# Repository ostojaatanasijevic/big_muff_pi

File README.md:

# Big Muff Pi clone

## Schematic

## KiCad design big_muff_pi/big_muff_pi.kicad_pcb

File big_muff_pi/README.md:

# Big Muff Pi clone

## Schematic

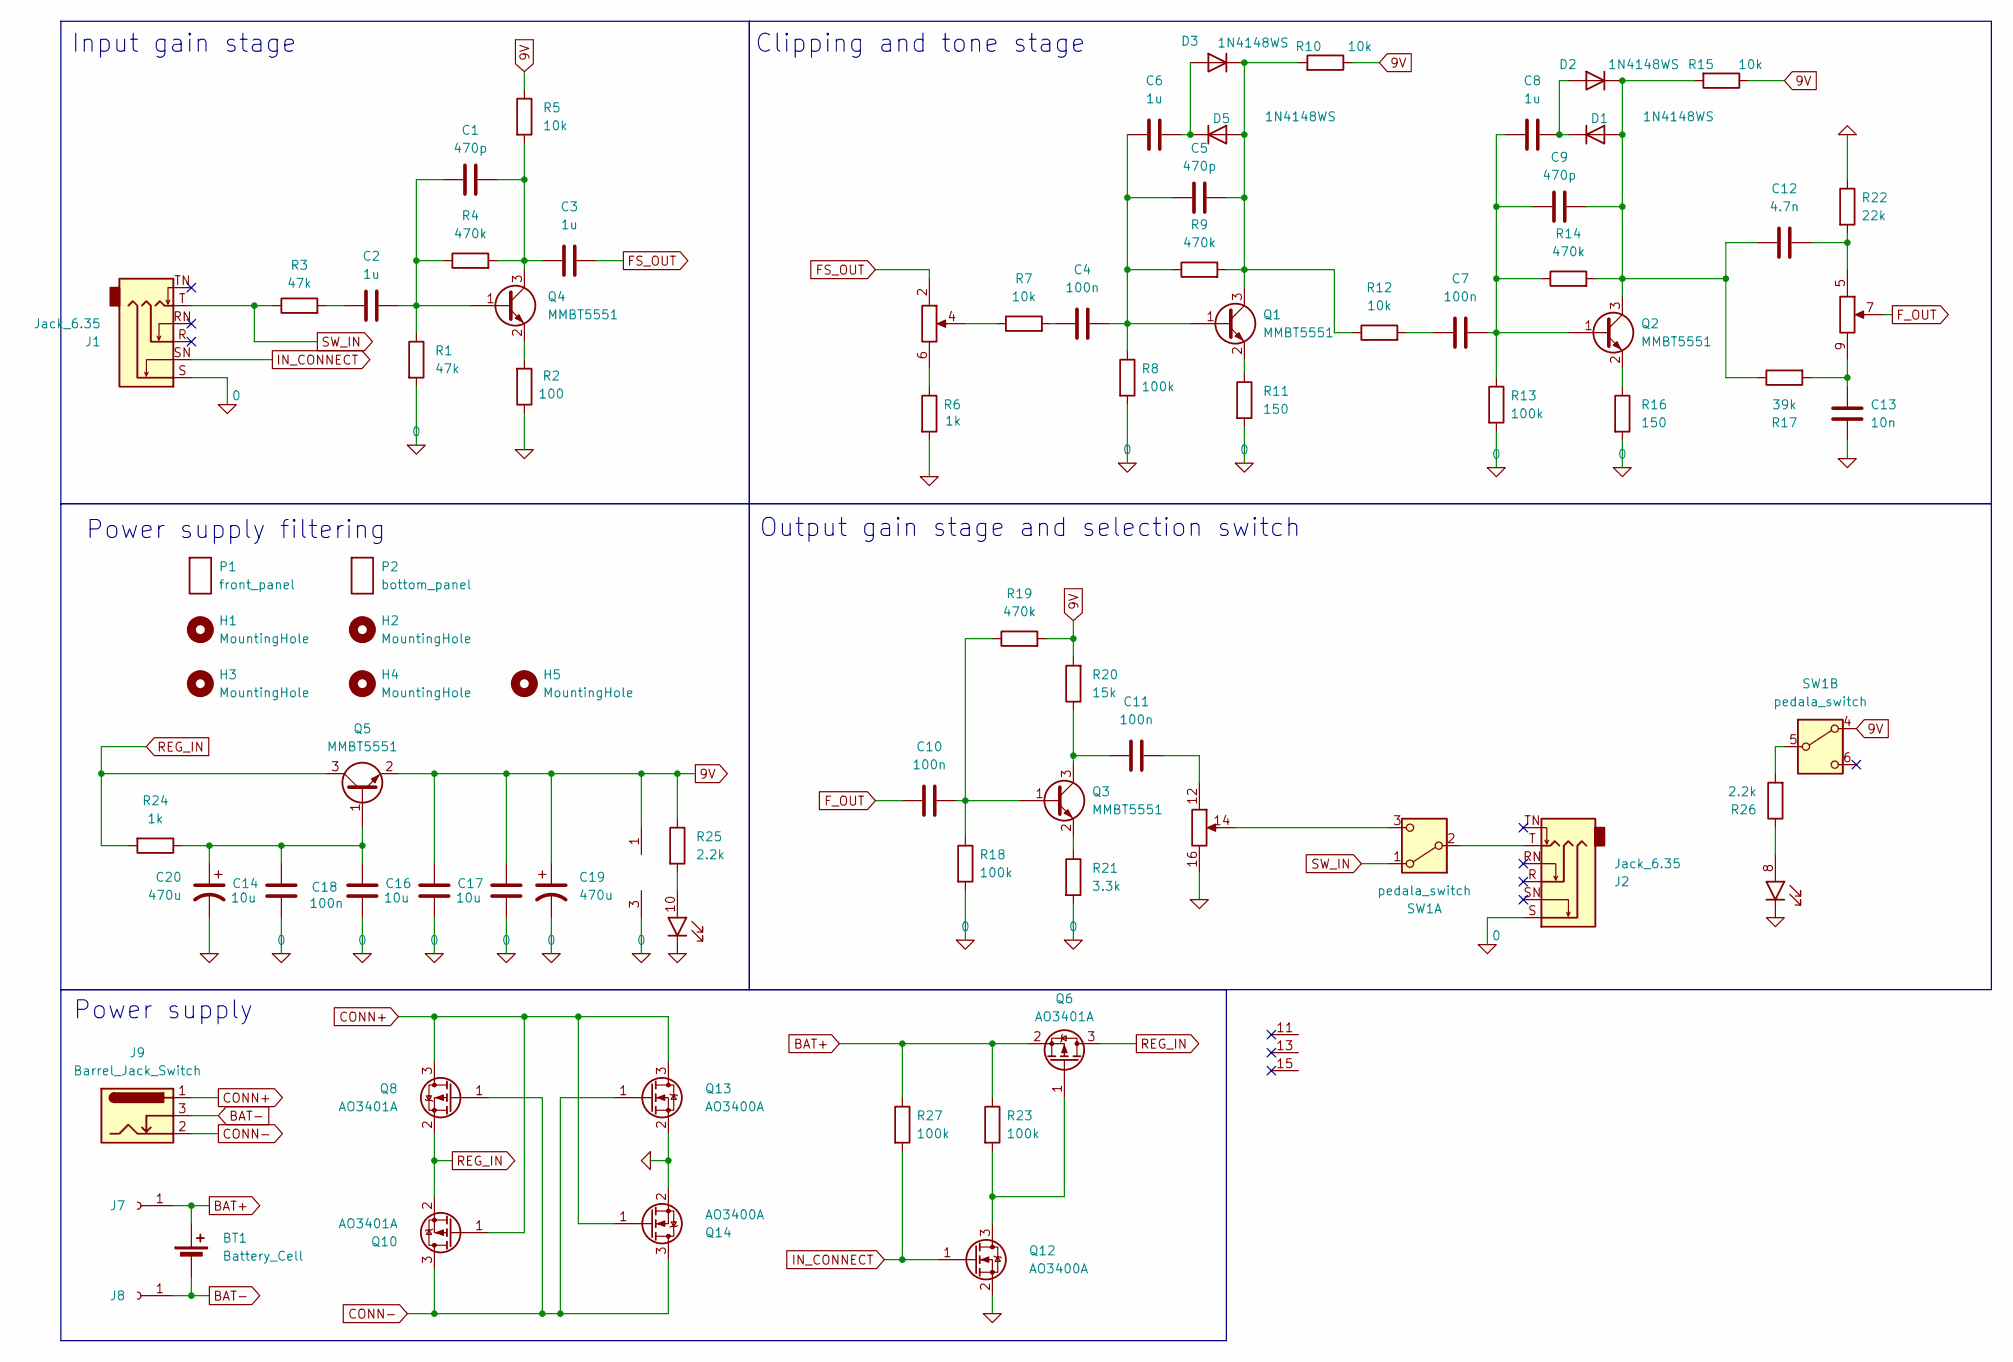
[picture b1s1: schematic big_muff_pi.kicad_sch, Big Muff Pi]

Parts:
BT1: Battery_Cell; BatteryHolder_Eagle_12BH611-GR
C1, C5, C9: 470p; C_0603_1608Metric_Pad1.08x0.95mm_HandSolder; LCSC C1620
C2, C3, C6, C8: 1u; C_0603_1608Metric_Pad1.08x0.95mm_HandSolder; LCSC C15849
C4, C7, C10, C11, C18: 100n; C_0603_1608Metric_Pad1.08x0.95mm_HandSolder; LCSC C14663
C12: 4.7n; C_0603_1608Metric_Pad1.08x0.95mm_HandSolder; LCSC C53987
C13: 10n; C_0603_1608Metric_Pad1.08x0.95mm_HandSolder; LCSC C57112
C14, C16, C17: 10u; C_0603_1608Metric_Pad1.08x0.95mm_HandSolder; LCSC C96446
C19, C20: 470u; CP_Radial_D8.0mm_P3.50mm
D1, D2, D3, D5: 1N4148WS; D_SOD-323; LCSC C2128
H1, H2, H3, H4, H5: MountingHole; M3_hole_with_spacer
J1, J2: Jack_6.35; Jack_6.35mm
J6: top_panel_connector; IDC-Header_2x08_P2.54mm_Vertical
J7, J8: Conn_01x01_Socket; TestPoint_THTPad_D2.5mm_Drill1.2mm
J9: Barrel_Jack_Switch; BarrelJack
P1: front_panel; front_plate
P2: bottom_panel; bottom_plate
Q1, Q2, Q3, Q4, Q5: MMBT5551; SOT-23; LCSC C2145
Q6, Q8, Q10: AO3401A; SOT-23; LCSC C15127
Q12, Q13, Q14: AO3400A; SOT-23; LCSC C20917
R1, R3: 47k; R_0603_1608Metric_Pad0.98x0.95mm_HandSolder; LCSC C25819
R2: 100; R_0603_1608Metric_Pad0.98x0.95mm_HandSolder; LCSC C22775
R4, R9, R14, R19: 470k; R_0603_1608Metric_Pad0.98x0.95mm_HandSolder; LCSC C23178
R5, R7, R10, R12, R15: 10k; R_0603_1608Metric_Pad0.98x0.95mm_HandSolder; LCSC C25804
R6, R24: 1k; R_0603_1608Metric_Pad0.98x0.95mm_HandSolder; LCSC C21190
R8, R13, R18, R23, R27: 100k; R_0603_1608Metric_Pad0.98x0.95mm_HandSolder; LCSC C25803
R11, R16: 150; R_0603_1608Metric_Pad0.98x0.95mm_HandSolder; LCSC C22808
R17: 39k; R_0603_1608Metric_Pad0.98x0.95mm_HandSolder; LCSC C23153
R20: 15k; R_0603_1608Metric_Pad0.98x0.95mm_HandSolder; LCSC C22809
R21: 3.3k; R_0603_1608Metric_Pad0.98x0.95mm_HandSolder; LCSC C22978
R22: 22k; R_0603_1608Metric_Pad0.98x0.95mm_HandSolder; LCSC C31850
R25, R26: 2.2k; R_0603_1608Metric_Pad0.98x0.95mm_HandSolder; LCSC C4190
SW1: pedala_switch; foot_switch_tht_no_pad

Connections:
0: C13.1, C14.2, C16.2, C17.2, C18.1, C19.2, C20.2, J1.S, J2.S, J6.3 (GND), J6.16, Q12.2 (S), Q13.2 (S), Q14.2 (S), R1.2, R2.1, R6.2, R8.2, R11.2, R13.2, R16.2, R18.2, R21.2, R22.1
9V: C16.1, C17.1, C19.1, J6.1 (VCC), Q5.2 (E), R5.1, R10.1, R15.1, R19.2, R20.2, R25.1, SW1.4 (A)
BAT+: BT1.1 (+), J7.1, Q6.2 (S), R23.1, R27.1
BAT-: BT1.2 (-), J8.1, J9.3
CONN+: J9.1, Q8.3 (D), Q10.1 (G), Q13.3 (D), Q14.1 (G)
CONN-: J9.2, Q8.1 (G), Q10.3 (D), Q13.1 (G), Q14.3 (D)
FS_OUT: C3.2, J6.2
F_OUT: C10.1, J6.7
IN_CONNECT: J1.SN, Q12.1 (G), R27.2
unnamed: C2.1, R3.2
unnamed: C4.1, R7.2
unnamed: C7.1, R12.2
unnamed: C9.2, C12.1, D1.2 (A), D2.1 (K), Q2.3 (C), R14.2, R15.2, R17.1
unnamed: C8.2, D1.1 (K), D2.2 (A)
unnamed: C6.2, D3.2 (A), D5.1 (K)
unnamed: C5.2, D3.1 (K), D5.2 (A), Q1.3 (C), R9.2, R10.2, R12.1
unnamed: J6.4, R7.1
unnamed: J6.6, R6.1
unnamed: C12.2, J6.5, R22.2
unnamed: C13.2, J6.9, R17.2
unnamed: C11.2, J6.12
unnamed: J6.14, SW1.3 (C)
unnamed: J6.8, R26.1
unnamed: J6.10, R25.2
unnamed: C4.2, C5.1, C6.1, Q1.1 (B), R8.1, R9.1
unnamed: Q1.2 (E), R11.1
unnamed: C7.2, C8.1, C9.1, Q2.1 (B), R13.1, R14.1
unnamed: Q2.2 (E), R16.1
unnamed: C10.2, Q3.1 (B), R18.1, R19.1
unnamed: C11.1, Q3.3 (C), R20.1
unnamed: Q3.2 (E), R21.1
unnamed: C1.1, C2.2, Q4.1 (B), R1.1, R4.1
unnamed: C1.2, C3.1, Q4.3 (C), R4.2, R5.2
unnamed: Q4.2 (E), R2.2
unnamed: C14.1, C18.2, C20.1, Q5.1 (B), R24.1
unnamed: Q6.1 (G), Q12.3 (D), R23.2
unnamed: J2.T, SW1.2 (B)
unnamed: R26.2, SW1.5 (B)
REG_IN: Q5.3 (C), Q6.3 (D), Q8.2 (S), Q10.2 (S), R24.2
SW_IN: J1.T, R3.1, SW1.1 (A)

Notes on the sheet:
Power supply filtering
Input gain stage
Output gain stage and selection switch
Clipping and tone stage
Power supply

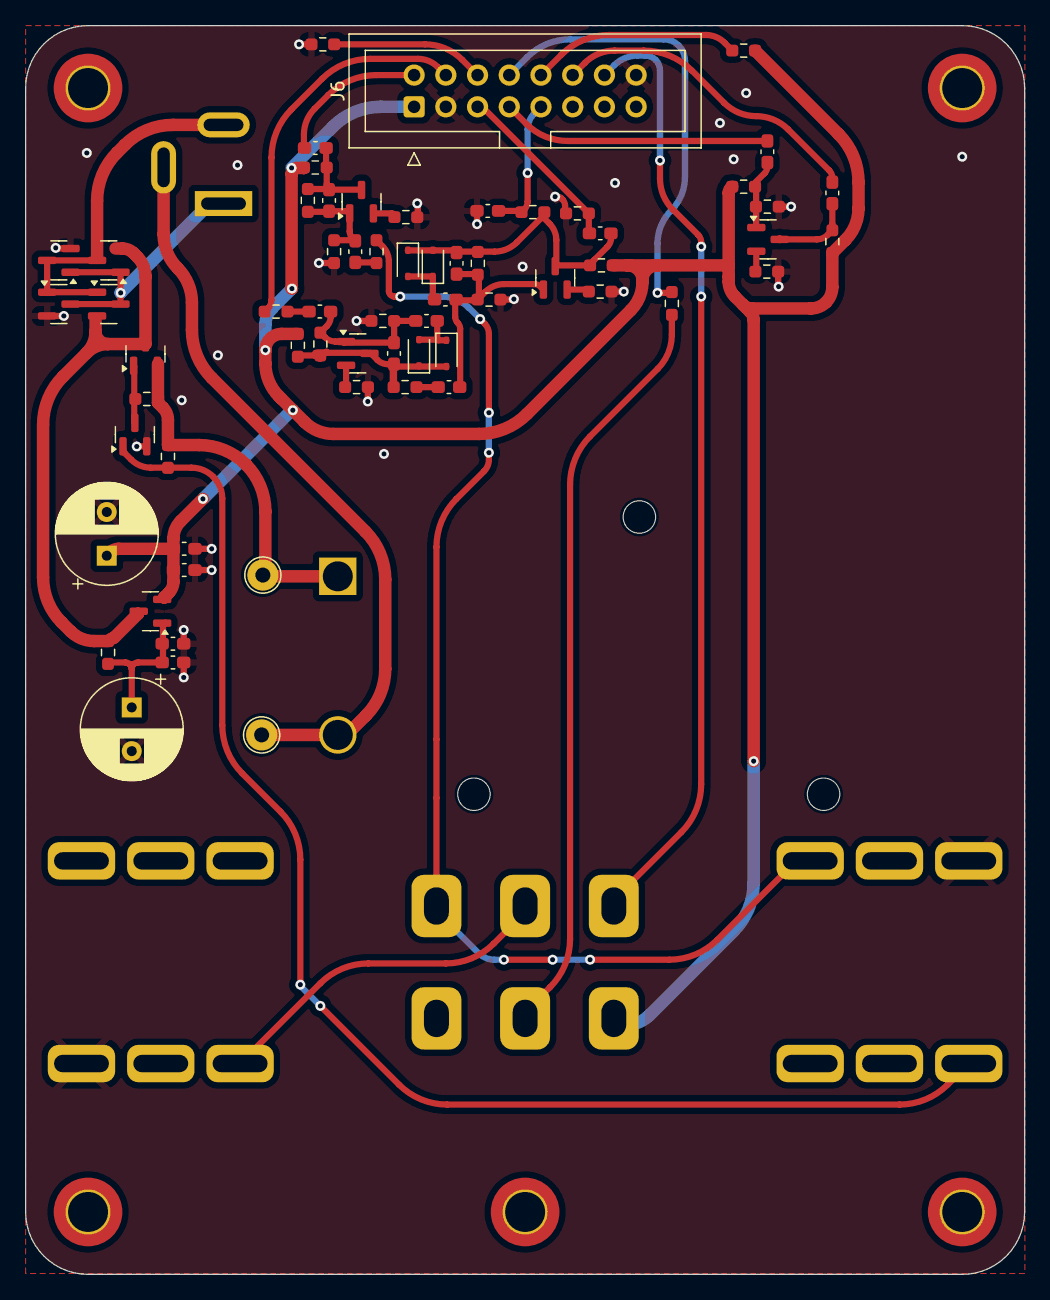
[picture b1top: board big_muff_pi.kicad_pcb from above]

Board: 2 copper layers, 80.0 x 100.0 mm, 78 parts (0 on the bottom side), 40 nets.

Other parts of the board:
D8: floating_green_led
D9: floating_red_led

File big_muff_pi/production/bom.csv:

Designator,Footprint,Quantity,Value,LCSC Part #
"C1, C5, C9",0603,3,470p,C1620
"C10, C11, C18, C4, C7",0603,5,100n,C14663
C12,0603,1,4.7n,C53987
C13,0603,1,10n,C57112
"C14, C16, C17",0603,3,10u,C96446
"C2, C3, C6, C8",0603,4,1u,C15849
"D1, D2, D3, D4, D5, D7",D_SOD-323,6,1N4148WS,C2128
"Q1, Q2, Q3, Q4, Q5",SOT-23,5,MMBT5551,C2145
"R1, R3",0603,2,47k,C25819
"R10, R12, R15, R5, R7",0603,5,10k,C25804
"R11, R16",0603,2,150,C22808
"R13, R18, R8",0603,3,100k,C25803
"R14, R19, R4, R9",0603,4,470k,C23178
R17,0603,1,39k,C23153
R2,0603,1,100,C22775
R20,0603,1,15k,C22809
R21,0603,1,3.3k,C22978
R22,0603,1,22k,C31850
"R24, R25, R26, R6",0603,4,1k,C21190

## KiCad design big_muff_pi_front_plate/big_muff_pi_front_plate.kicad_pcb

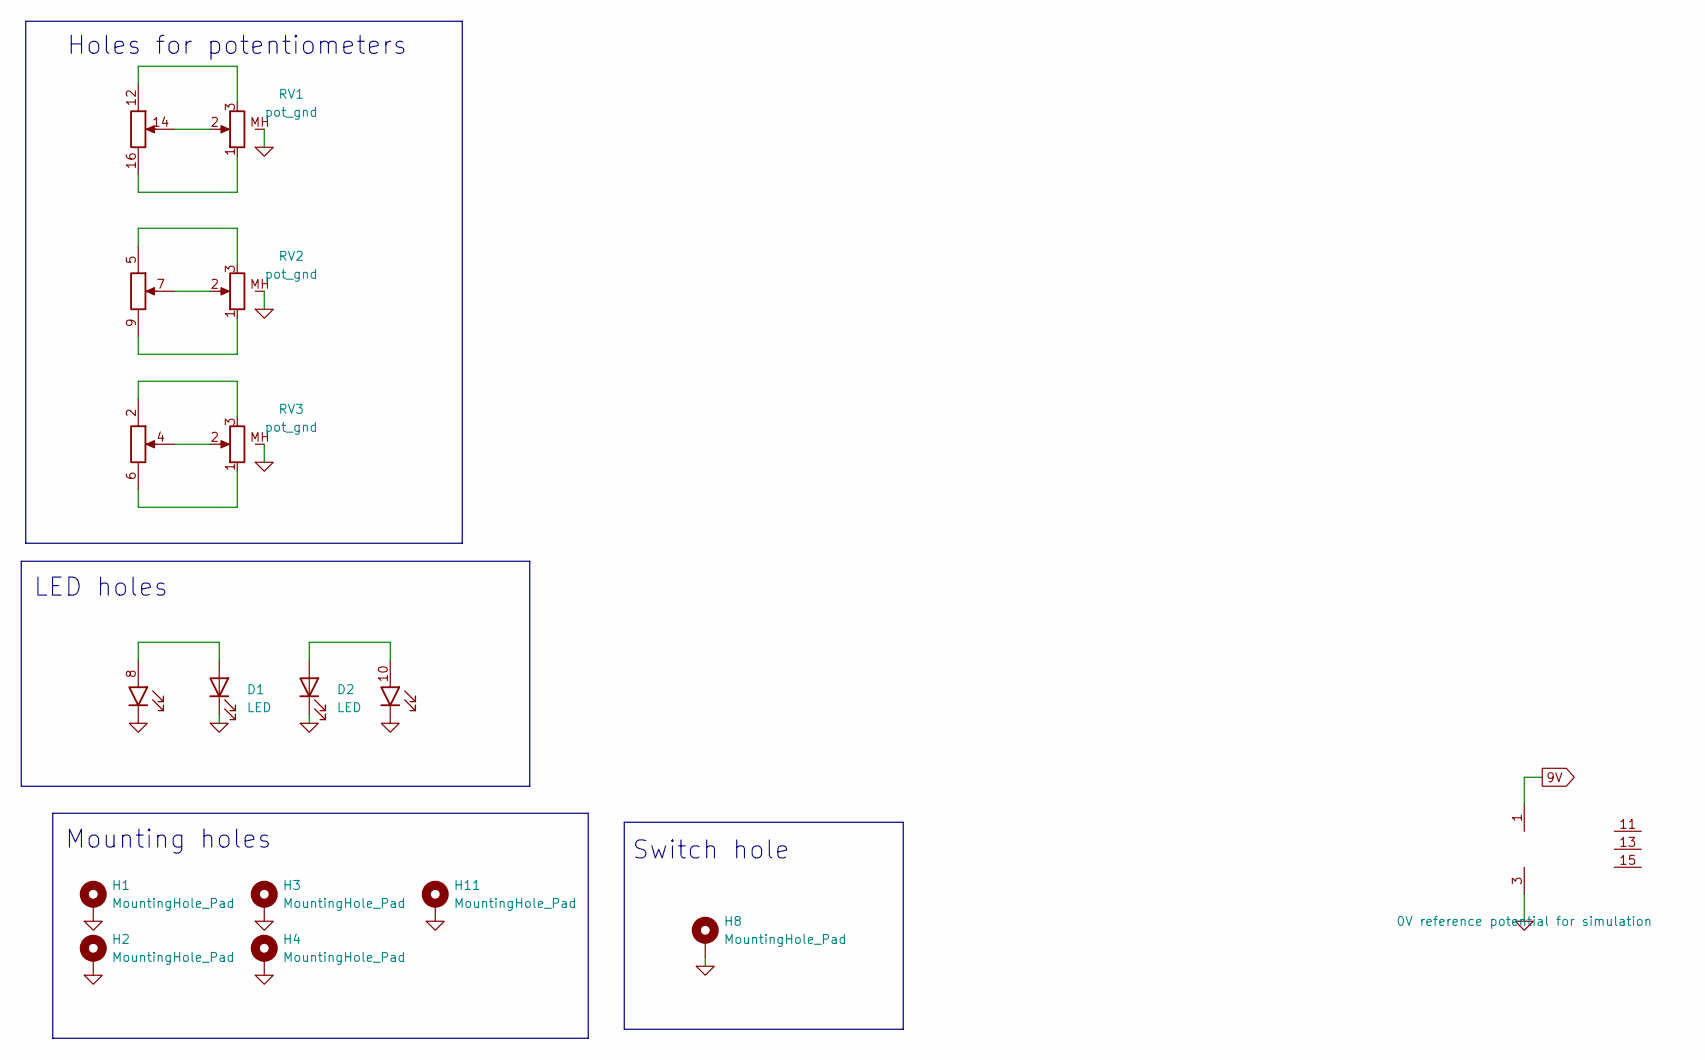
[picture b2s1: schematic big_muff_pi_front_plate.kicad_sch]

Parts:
D1: LED; red_led
D2: LED; green_led
H1, H2, H3, H4, H11: MountingHole_Pad; MountingHole_3.2mm_M3_DIN965_Pad_TopBottom
H8: MountingHole_Pad; plated_switch_hole
J1: top_panel_connector; IDC-Header_2x08_P2.54mm_Vertical
RV1, RV2, RV3: pot_gnd; top_plate_pot

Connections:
0: D1.1 (K), D2.1 (K), H1.1, H2.1, H3.1, H4.1, H8.1, H11.1, J1.3 (GND), RV1.MH (2), RV2.MH (2), RV3.MH (2)
9V: J1.1 (VCC)
unnamed: D1.2 (A), J1.8
unnamed: D2.2 (A), J1.10
unnamed: J1.2, RV3.3
unnamed: J1.4, RV3.2
unnamed: J1.6, RV3.1
unnamed: J1.5, RV2.3
unnamed: J1.7, RV2.2
unnamed: J1.9, RV2.1
unnamed: J1.12, RV1.3
unnamed: J1.14, RV1.2
unnamed: J1.16, RV1.1

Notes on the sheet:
Mounting holes
Switch hole
LED holes
Holes for potentiometers

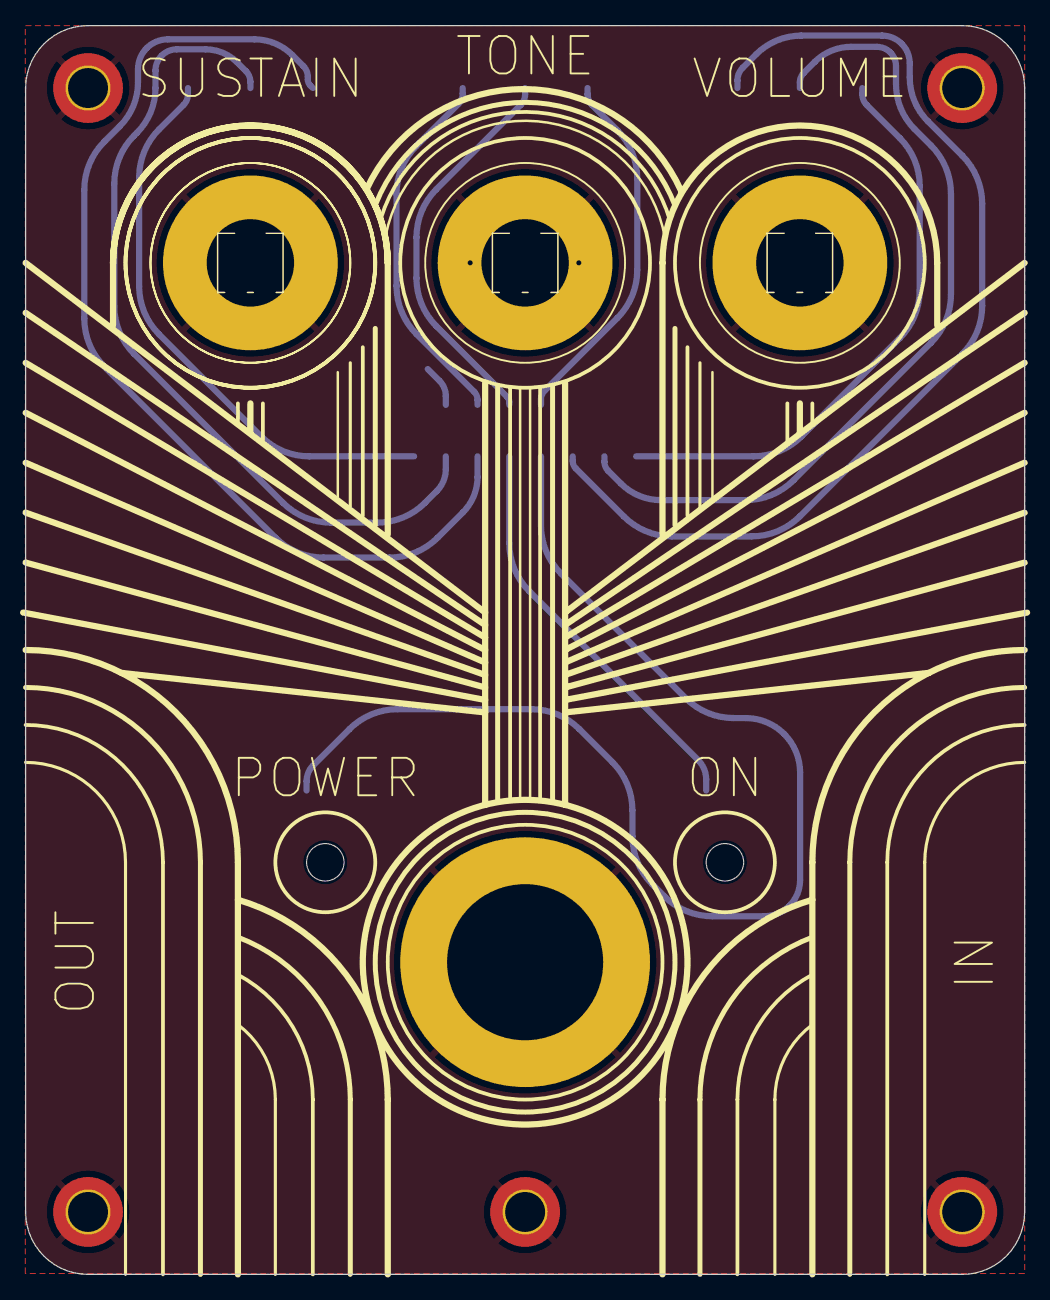
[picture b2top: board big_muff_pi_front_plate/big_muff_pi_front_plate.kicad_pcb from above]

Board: 2 copper layers, 80.0 x 100.0 mm, 12 parts (1 on the bottom side), 12 nets.

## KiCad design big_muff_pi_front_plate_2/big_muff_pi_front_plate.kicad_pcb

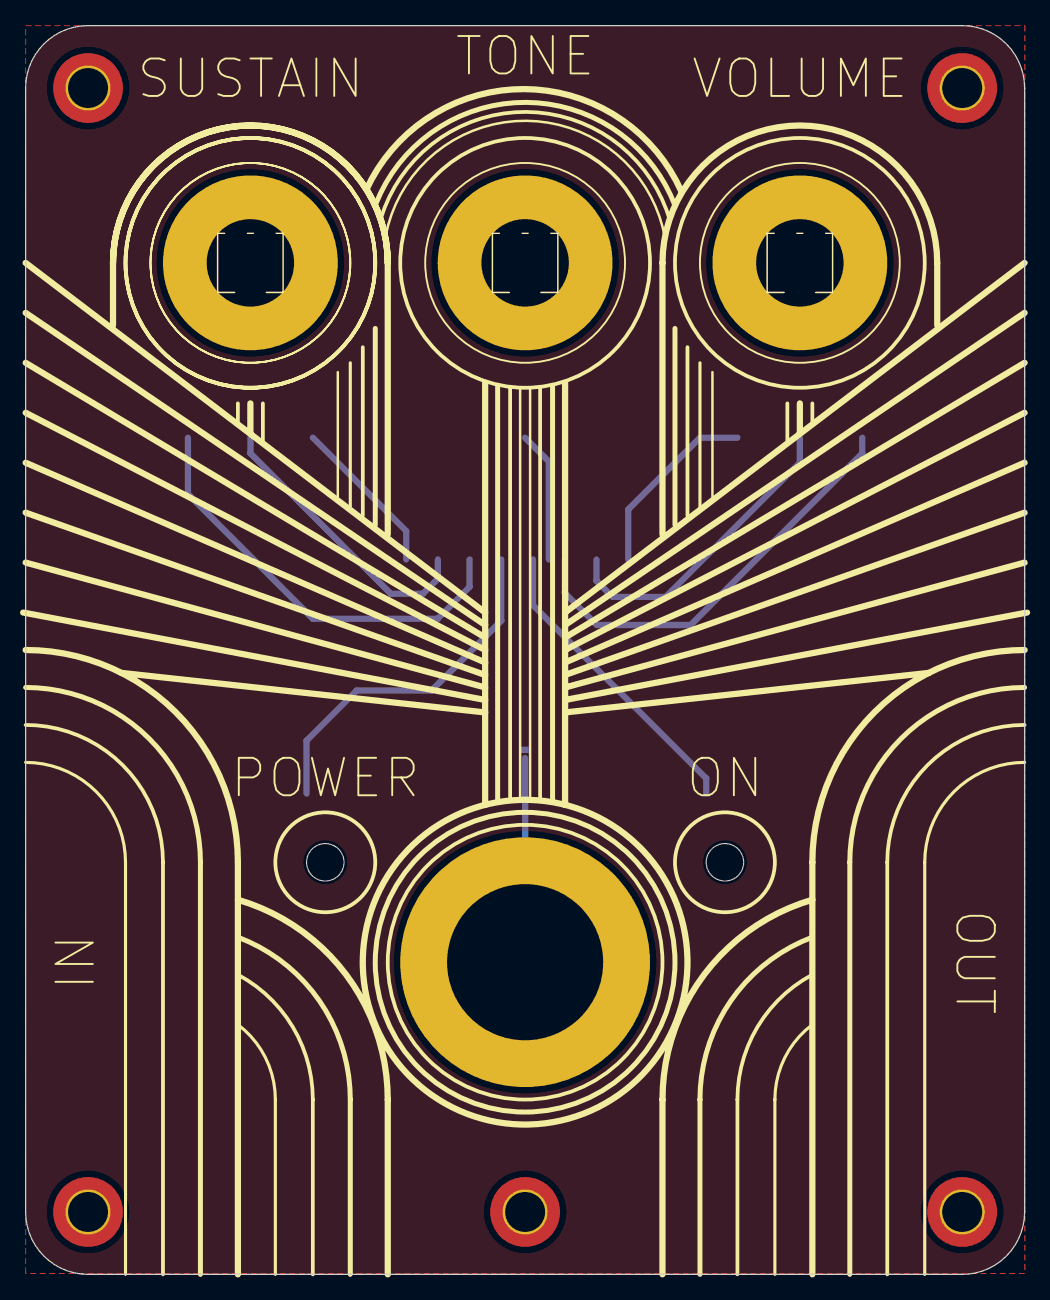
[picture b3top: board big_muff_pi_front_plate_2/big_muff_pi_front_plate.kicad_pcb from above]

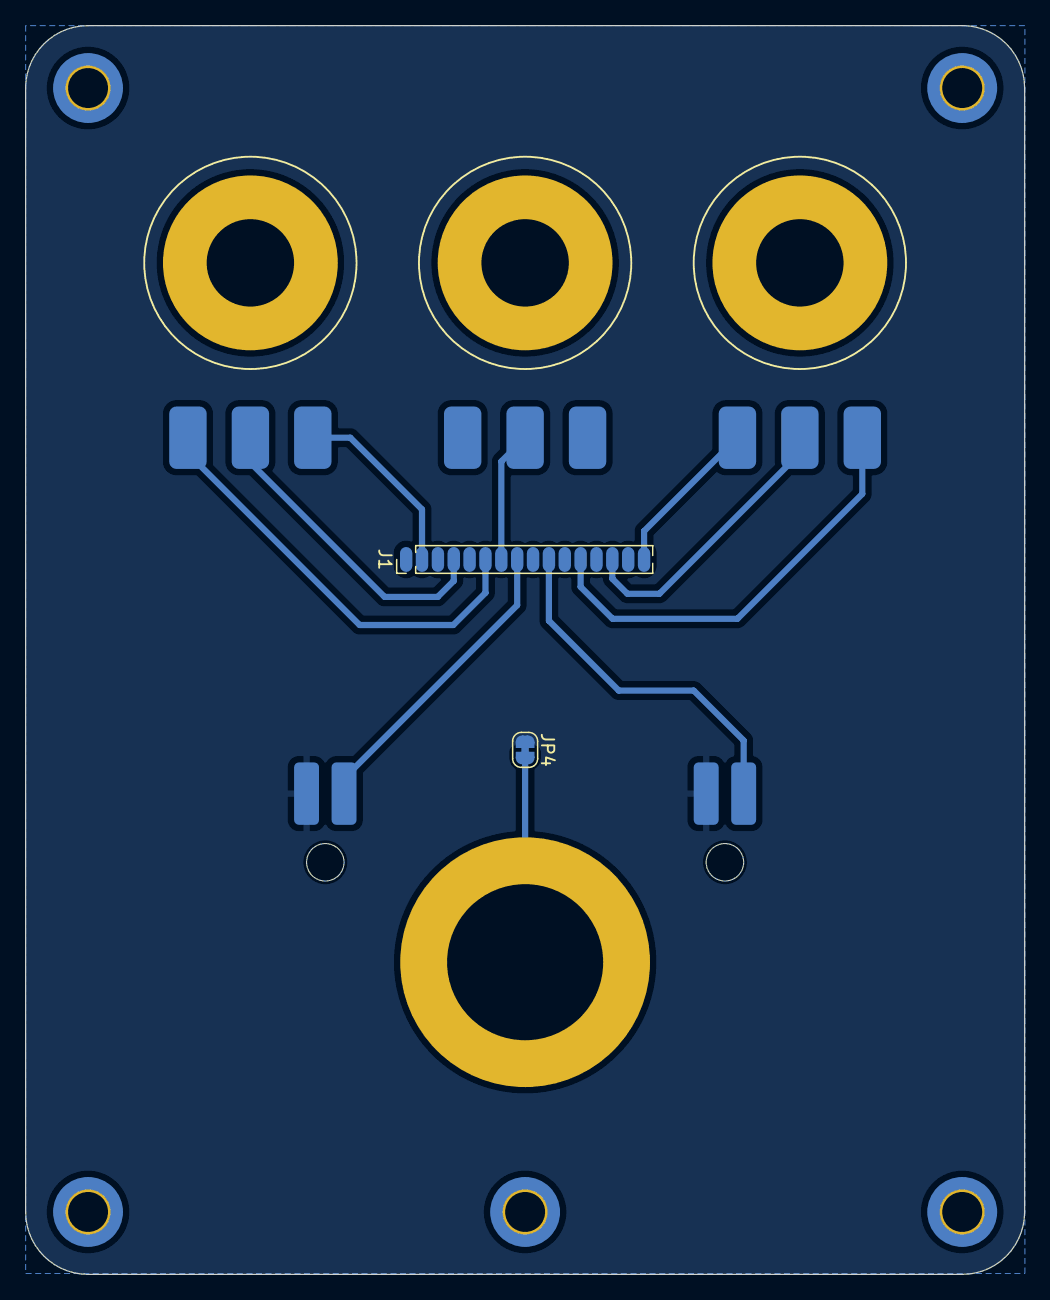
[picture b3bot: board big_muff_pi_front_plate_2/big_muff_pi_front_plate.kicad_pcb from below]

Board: 2 copper layers, 80.0 x 100.0 mm, 13 parts (2 on the bottom side), 13 nets.

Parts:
D1: LED; red_led
D2: LED; green_led
H1, H2, H3, H4, H11: MountingHole; MountingHole_3.2mm_M3_DIN965_Pad_TopBottom
H8: MountingHole_Pad; plated_switch_hole
J1: top_panel_connector; bottom_connector
JP4: SolderJumper_2_Bridged; SolderJumper-2_P1.3mm_Bridged_RoundedPad1.0x1.5mm
RV1, RV2, RV3: R_Potentiometer; top_plate_pot

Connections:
0: D1.1 (K), D2.1 (K), JP4.1 (A)
unnamed: D1.2 (A), J1.8
unnamed: D2.2 (A), J1.10
unnamed: J1.2, RV1.1
unnamed: J1.4, RV1.2
unnamed: J1.6, RV1.3
unnamed: J1.5, RV2.1
unnamed: J1.7, RV2.2
unnamed: J1.9, RV2.3
unnamed: J1.12, RV3.1
unnamed: J1.14, RV3.2
unnamed: J1.16, RV3.3
unnamed: H8.1, JP4.2 (B)

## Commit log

2025-04-01 Estetics finalized.
2025-04-01 Only routing left.
2025-04-01 README.
2025-04-01 README update.
2025-04-01 upd.
2025-04-02 Updated images.
2025-04-02 Lib sync.
2025-04-03 New switch
2025-04-03 poredjane komponente
2025-04-03 rutiranje v1
2025-04-03 rutiranje v2.
2025-04-03 Tiny changes.
2025-04-05 Updated library.
2025-04-05 Updated libs.
2025-04-05 Production files v1.
2025-04-20 Rotated 6.35 pins, switched connector positions, switched LED.
2025-05-05 Added IDC, added front plate.
2025-05-05 Libre
2025-05-05 New footpritn
2025-05-05 Top plate work.
2025-05-05 Led done
    Led done
2025-05-05 Linked lib
2025-05-05 Added PMOS.
2025-05-05 Added the full wave rectifier.
2025-05-05 Neater.
2025-05-06 Renamed because woke.
2025-05-06 Returned to normal because trad.
2025-05-06 Inputs rotated, power conn moved, spacers updated.
2025-05-09 Pots rotated, more space for the battery.
2025-05-09 Updated lib.
2025-05-10 Potentiometers checked, LED updated
2025-05-10 Added the bottom plate.
2025-05-10 small work
2025-05-11 Larger logo, bottom plate silkscreen.
2025-05-12 Solid pro grass lol.
2025-05-13 Updated 3d models.
2025-05-13 Update 3d model.
2025-05-13 Gen 3d body script.
2025-05-13 small.
2025-05-13 Slight modl
2025-05-14 idk.
2025-05-19 Front plate update.
2025-05-19 I LOVE U
2025-05-19 anin update.
2025-05-19 small mods.
2025-05-21 New switch, fixed courtyards.
2025-05-21 Big muff pi, new connector position.
2025-05-21 Updated traces.
2025-05-21 Main board almost ready.
2025-05-21 Front plate update, componets created.
2025-05-21 Updated 3D bodies.
2025-05-21 Front plate trace done.
2025-05-22 Rounded traces.
2025-05-22 Rounded traces za front plate.
2025-05-22 2.2k LED.
2025-05-22 Pot labels.
2025-05-22 dfasdf dfasdf
2025-05-22 dsfa
2025-05-24 Production ready.
2025-05-24 READM
